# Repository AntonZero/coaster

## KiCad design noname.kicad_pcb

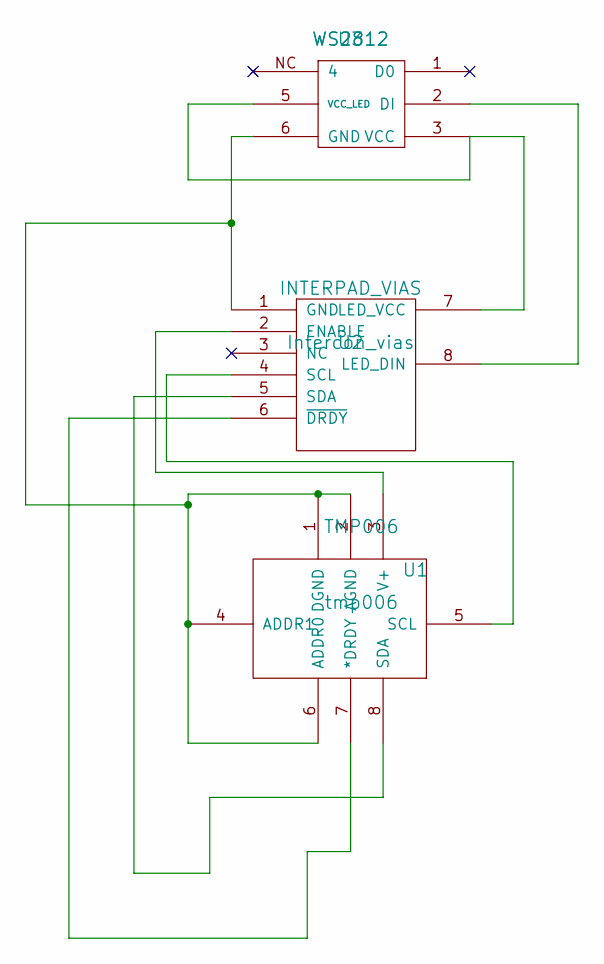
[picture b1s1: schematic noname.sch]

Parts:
U1: TMP006; tmp006
U2: INTERPAD_VIAS; Intercon_vias
U3: WS2812

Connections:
unnamed: U1.5 (SCL), U2.4 (SCL)
unnamed: U2.7 (LED_VCC), U3.3 (VCC), U3.5 (VCC_LED)
unnamed: U2.8 (LED_DIN), U3.2 (DI)
unnamed: U1.7 (*DRDY), U2.6 (~DRDY)
unnamed: U1.3 (V+), U2.2 (ENABLE)
unnamed: U1.8 (SDA), U2.5 (SDA)
unnamed: U1.1 (DGND), U1.2 (AGND), U1.4 (ADDR1), U1.6 (ADDR0), U2.1 (GND), U3.6 (GND)

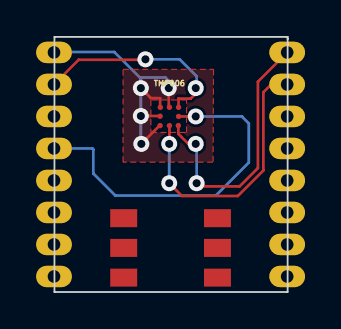
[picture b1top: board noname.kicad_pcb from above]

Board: 2 copper layers, 13.0 x 14.2 mm, 4 parts (0 on the bottom side), 7 nets.

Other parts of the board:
Intercon_vias: VAL**; Intercon_vias

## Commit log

2014-09-12 :octocat: Added .gitattributes & .gitignore files
2014-09-12 test
